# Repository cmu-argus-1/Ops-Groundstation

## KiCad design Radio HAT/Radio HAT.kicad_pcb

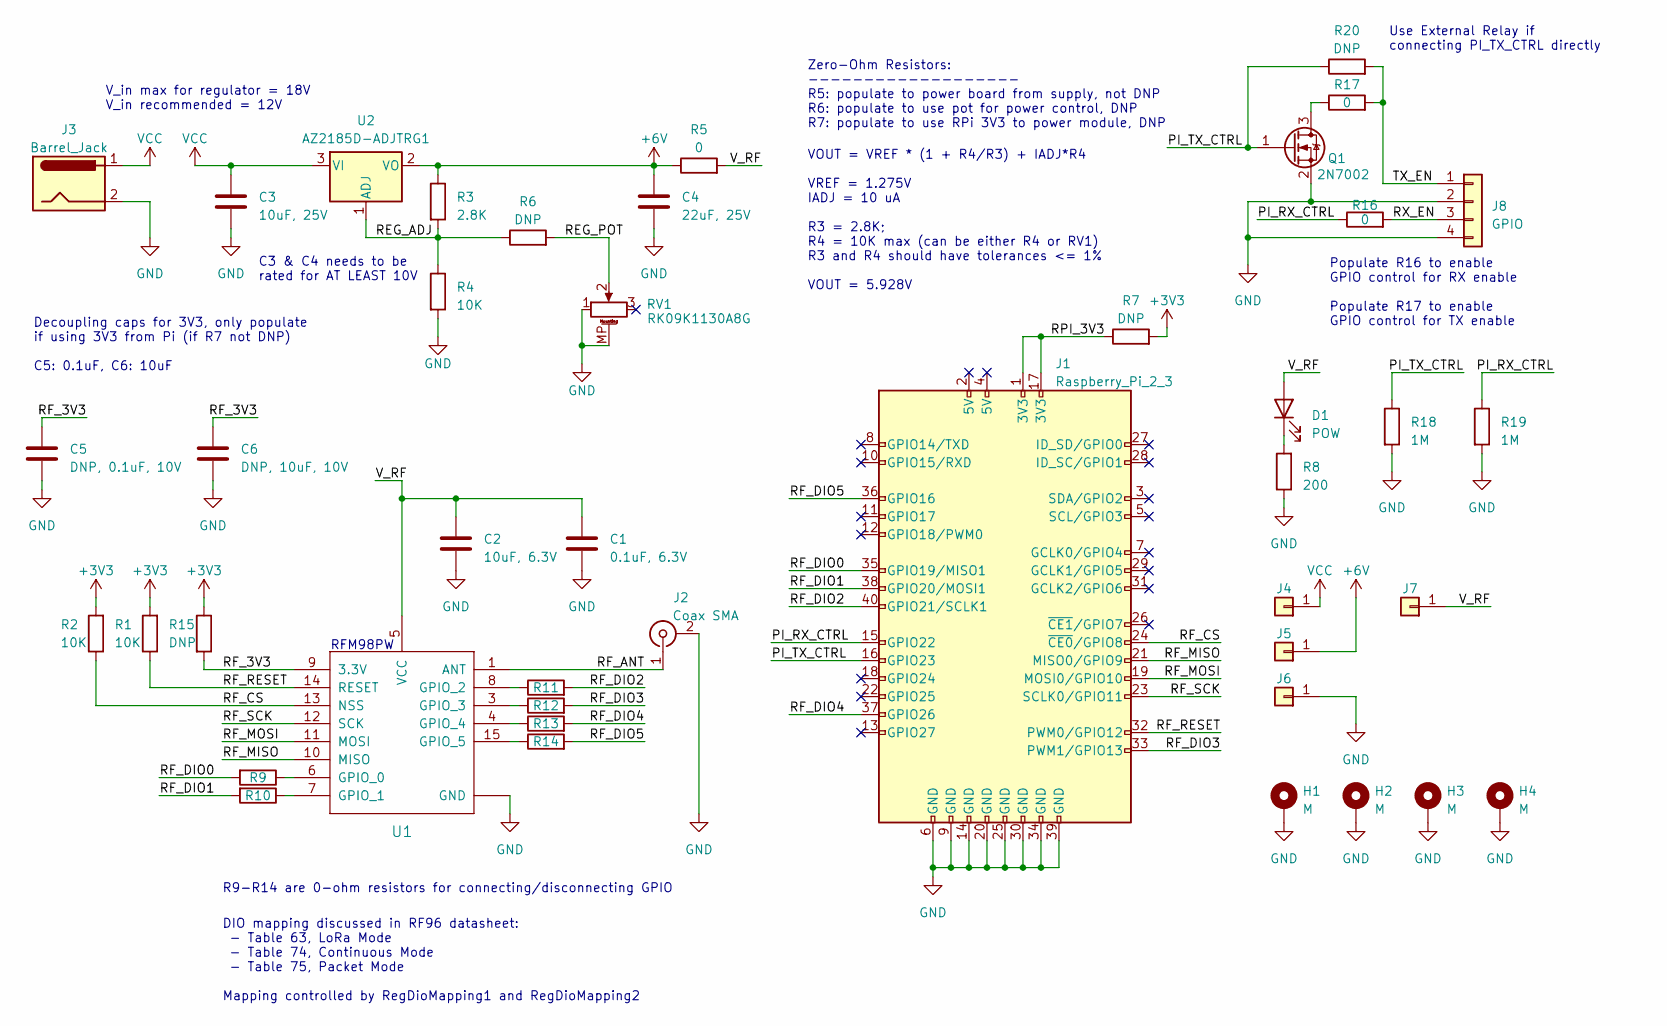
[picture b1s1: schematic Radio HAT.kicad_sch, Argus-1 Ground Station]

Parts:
C1: 0.1uF, 6.3V; C_0603_1608Metric_Pad1.08x0.95mm_HandSolder
C2: 10uF, 6.3V; C_0603_1608Metric_Pad1.08x0.95mm_HandSolder
C3: 10uF, 25V; C_0805_2012Metric_Pad1.18x1.45mm_HandSolder
C4: 22uF, 25V; C_0805_2012Metric_Pad1.18x1.45mm_HandSolder
C5: DNP, 0.1uF, 10V; C_0603_1608Metric_Pad1.08x0.95mm_HandSolder
C6: DNP, 10uF, 10V; C_0603_1608Metric_Pad1.08x0.95mm_HandSolder
D1: POW; LED_0805_2012Metric_Pad1.15x1.40mm_HandSolder
H1, H2, H3, H4: M; MountingHole_2.7mm_M2.5_Pad_Via
J1: Raspberry_Pi_2_3; PinSocket_2x20_P2.54mm_Vertical
J2: Coax SMA; SMA_Amphenol_901-144_Vertical
J3: Barrel_Jack; BarrelJack_Horizontal
J4: VCC; TestPoint_Loop_D2.50mm_Drill1.0mm
J5: 6V; TestPoint_Loop_D2.50mm_Drill1.0mm
J6: GND; TestPoint_Loop_D2.50mm_Drill1.0mm
J7: V_RF; TestPoint_Loop_D2.50mm_Drill1.0mm
J8: GPIO; TerminalBlock_TE_282834-4_1x04_P2.54mm_Horizontal
Q1: 2N7002; SOT-23
R1, R2, R4: 10K; R_0805_2012Metric_Pad1.20x1.40mm_HandSolder
R3: 2.8K; R_0805_2012Metric_Pad1.20x1.40mm_HandSolder
R5: 0; R_1210_3225Metric_Pad1.30x2.65mm_HandSolder
R6, R7, R15, R20: DNP; R_0805_2012Metric_Pad1.20x1.40mm_HandSolder
R8: 200; R_0805_2012Metric_Pad1.20x1.40mm_HandSolder
R9, R10, R11, R12, R13, R14, R16, R17: 0; R_0805_2012Metric_Pad1.20x1.40mm_HandSolder
R18, R19: 1M; R_0805_2012Metric_Pad1.20x1.40mm_HandSolder
RV1: RK09K1130A8G; Potentiometer_Alps_RK09K_Single_Vertical
U1: RFM98PW; RFM95PW
U2: AZ2185D-ADJTRG1; TO-252-2

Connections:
+3V3: R1.2, R2.2, R7.2, R15.1
+6V: C4.1, J5.1, R3.1, R5.1, U2.2 (VO)
/PI_RX_CTRL: J1.15 (GPIO22), R16.1, R19.1
/PI_TX_CTRL: J1.16 (GPIO23), Q1.1 (G), R18.1, R20.1
/REG_ADJ: R3.2, R4.1, R6.1, U2.1 (ADJ)
/REG_POT: R6.2, RV1.2
/RF_3V3: C5.1, C6.1, R15.2, U1.9 (3.3V)
/RF_ANT: J2.1 (In), U1.1 (ANT)
/RF_CS: J1.24 (~CE0/GPIO8), R2.1, U1.13 (NSS)
/RF_DIO0: J1.35 (GPIO19/MISO1), R9.2
/RF_DIO1: J1.38 (GPIO20/MOSI1), R10.2
/RF_DIO2: J1.40 (GPIO21/SCLK1), R11.2
/RF_DIO3: J1.33 (PWM1/GPIO13), R12.2
/RF_DIO4: J1.37 (GPIO26), R13.2
/RF_DIO5: J1.36 (GPIO16), R14.2
/RF_MISO: J1.21 (MISO0/GPIO9), U1.10 (MISO)
/RF_MOSI: J1.19 (MOSI0/GPIO10), U1.11 (MOSI)
/RF_RESET: J1.32 (PWM0/GPIO12), R1.1, U1.14 (RESET)
/RF_SCK: J1.23 (SCLK0/GPIO11), U1.12 (SCK)
/RPI_3V3: J1.1 (3V3), J1.17 (3V3), R7.1
/RX_EN: J8.3, R16.2
/TX_EN: J8.1, R17.2, R20.2
/V_RF: C1.1, C2.1, D1.2 (A), J7.1, R5.2, U1.5 (VCC)
GND: C1.2, C2.2, C3.2, C4.2, C5.2, C6.2, H1.1, H2.1, H3.1, H4.1, J1.6 (GND), J1.9 (GND), J1.14 (GND), J1.20 (GND), J1.25 (GND), J1.30 (GND), J1.34 (GND), J1.39 (GND), J2.2 (Ext), J3.2, J6.1, J8.2, J8.4, Q1.2 (S), R4.2, R8.1, R18.2, R19.2, RV1.1, RV1.MP (MountPin), U1.2 (GND), U1.16 (GND), U1.17 (GND)
unnamed: D1.1 (K), R8.2
unnamed: Q1.3 (D), R17.1
unnamed: R9.1, U1.6 (GPIO_0)
unnamed: R10.1, U1.7 (GPIO_1)
unnamed: R11.1, U1.8 (GPIO_2)
unnamed: R12.1, U1.3 (GPIO_3)
unnamed: R13.1, U1.4 (GPIO_4)
unnamed: R14.1, U1.15 (GPIO_5)
VCC: C3.1, J3.1, J4.1, U2.3 (VI)

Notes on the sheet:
Populate R16 to enable GPIO control for RX enable Populate R17 to enable GPIO control for TX enable
Decoupling caps for 3V3, only populate if using 3V3 from Pi (if R7 not DNP) C5: 0.1uF, C6: 10uF
DIO mapping discussed in RF96 datasheet: - Table 63, LoRa Mode - Table 74, Continuous Mode - Table 75, Packet Mode Mapping controlled by RegDioMapping1 and RegDioMapping2
Zero-Ohm Resistors: ------------------- R5: populate to power board from supply, not DNP R6: populate to use pot for power control, DNP R7: populate to use RPi 3V3 to power module, DNP
V_in max for regulator = 18V V_in recommended = 12V
RFM98PW
R9-R14 are 0-ohm resistors for connecting/disconnecting GPIO
C3 & C4 needs to be rated for AT LEAST 10V
Use External Relay if connecting PI_TX_CTRL directly
VOUT = VREF * (1 + R4/R3) + IADJ*R4 VREF = 1.275V IADJ = 10 uA R3 = 2.8K; R4 = 10K max (can be either R4 or RV1) R3 and R4 should have tolerances <= 1% VOUT = 5.928V

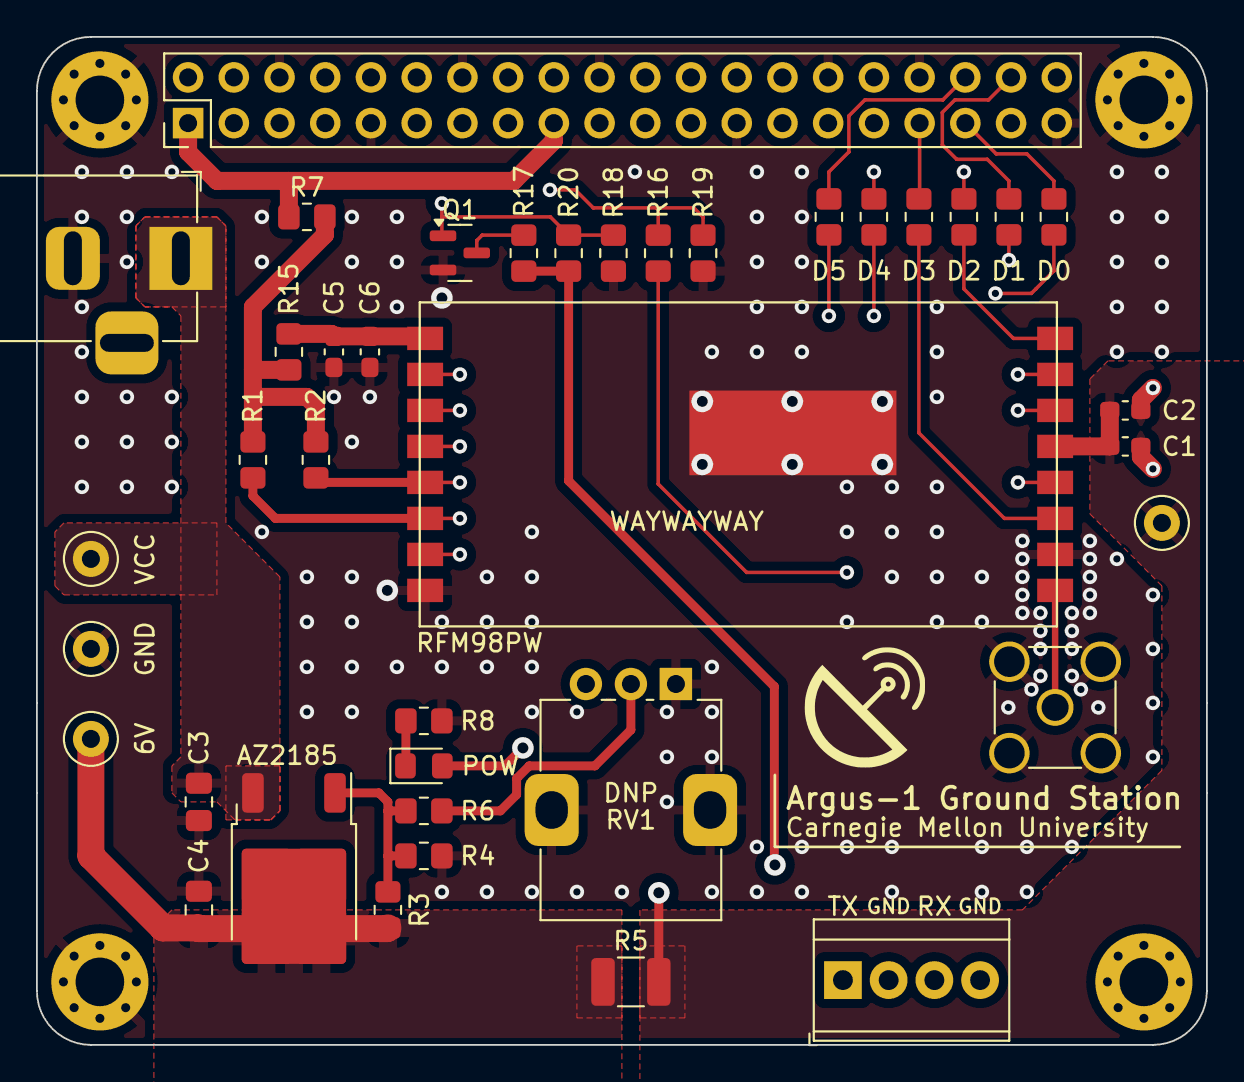
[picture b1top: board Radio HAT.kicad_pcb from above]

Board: 4 copper layers, 65.0 x 56.0 mm, 43 parts (0 on the bottom side), 33 nets.

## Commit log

2024-04-18 Changes for v1.2
2024-05-02 Fixed TX and RX enable circuits
2024-05-05 Added stitching vias
2024-05-26 Add bypass resistor on TX GPIO control, ground Pot
2024-05-26 Export new BOM
2024-09-25 Fixed Q1 footprint

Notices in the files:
Radio HAT/Radio HAT.kicad_pcb:
LICENSE: CC BY 4.0
